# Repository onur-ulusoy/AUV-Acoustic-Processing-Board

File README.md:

# Acoustic Processing Board (APB) Hardware

The Acoustic Processing Board (APB) is a specialized hardware project devoted to processing underwater acoustic signals, captured via hydrophones. This repository houses the electronic design and hardware specifications needed to construct or adapt the APB. Serving as a crucial tool for underwater exploration, navigation, and communication, the APB stands as a testament to innovative engineering solutions. This project is developed for ITU AUV Team.

<picture>    </picture>

<p align="center"><em >APB Filter Test Board</em></p>

<picture>    </picture>

<p align="center">
    
</p>

<p align="center"><em >AUV Electronics 2022</em></p>

<picture>    </picture>

<p align="center">
    
</p>

<picture>    </picture>

<picture>    </picture>

## Table of Contents
- [Acoustic Processing Board (APB) Hardware](#acoustic-processing-board-apb-hardware)
  - [Table of Contents](#table-of-contents)
  - [Project Description](#project-description)
  - [Electronics Design](#electronics-design)
    - [Hydrophone Biasing](#hydrophone-biasing)
    - [Pre-Amplification](#pre-amplification)
    - [6 Pole Butterworth Bandpass Filter](#6-pole-butterworth-bandpass-filter)
    - [Analog Power Supply](#analog-power-supply)
    - [ADC Buffering](#adc-buffering)
  - [Simulation](#simulation)
  - [Filter Test Board](#filter-test-board)
    - [Layer Structure](#layer-structure)
    - [Manufacturing](#manufacturing)
  - [Digital Part](#digital-part)
  - [Technologies Used](#technologies-used)
  - [License](#license)
  - [Project Timeline](#project-timeline)
  - [Gallery](#gallery)

## Project Description

The Acoustic Processing Board (APB) is a pivotal development in the field of Autonomous Underwater Vehicles (AUVs), designed to accurately detect the positions of underwater objects. To optimize performance, APB is split into two distinct parts: an analog PCB and a digital PCB.

The focus of this repository is the analog PCB, which primarily serves as a bandpass filter for frequencies between 25 and 40kHz. This PCB is designed to filter incoming signals from hydrophones before they are passed onto the digital component of the APB. The board was meticulously designed and simulated using LTspice software, featuring components from Analog Devices. The physical layout of the PCB was then accomplished using Altium Designer.

In addition to the analog PCB, there is a complementary digital PCB. This board is responsible for processing the filtered signals from three hydrophones to determine the location of objects underwater. It employs Fast Fourier Transform (FFT) algorithms for signal processing, and is powered by an STM32 microcontroller.

In the interest of thorough testing and performance optimization, the first iteration of the filter PCB was designed for a single hydrophone. This approach enables focused testing on the filtering capabilities, allowing for incremental improvements and fine-tuning of the board's performance before scaling to a three-hydrophone system.

The APB is a testament to innovative design, offering a unique approach to signal processing for AUVs. It represents a significant contribution to our understanding and exploration of underwater environments. We encourage you to explore the repository, understand the design, and contribute to the ongoing development of this cutting-edge technology.

<picture>    </picture>

## Electronics Design

The APB Analog's design is a combination of intricate electronic engineering concepts and high-precision layout work. For an in-depth understanding of its composition, be sure to check the [Full schematics](/LTSpice_Simulation/Full%20Schematic.pdf) and [PCB Schematic Sheets](/Schematic%20Sheets/) These documents not only delineate the arrangement and interconnectivity of the board's components, but also offer insightful details about their specific roles and functionalities. Whether you're interested in the bandpass filtering process, power distribution, or the input/output interfaces, the schematic sheets hold the key to understanding the APB Analog's operational architecture.

### Hydrophone Biasing 

Hydrophone biasing is the first stage in our APB design, and it's vital to the overall functionality of the system. For each of the three hydrophones, a Vhyd- and Vhyd+ and Vcc are the inputs, while Vampin is the output. Importantly, Vhyd- is grounded. This arrangement ensures the correct biasing of the hydrophones, setting the correct operating point for each device and allowing for the effective conversion of underwater acoustic signals into electrical signals.

<p align="center">
    
</p>

### Pre-Amplification

The pre-amplification stage is another essential component of our APB design, ensuring that the electrical signals produced by the hydrophones are amplified adequately for further processing. This stage also employs three separate units, one for each hydrophone. Vampin is used as the input, while Vfin serves as the output. The pre-amplifier is driven by a high precision op-amp, ensuring low-noise amplification and thereby enhancing the clarity and resolution of the captured signals.

<p align="center">
    
</p>

### 6 Pole Butterworth Bandpass Filter

To further process the amplified signals, we employ a 6-pole Butterworth bandpass filter. This filter is replicated three times, once for each hydrophone. The selection of this specific filter topology allows for a flat frequency response in the passband, and a fast roll-off rate, making it highly suitable for our signal processing needs. Appropriate capacitor and resistor values were determined using Analog Devices' application notes. The filter takes Vfin as an input and outputs a filtered signal, Vfout. Each operational amplifier in this stage is referenced with Agnd, which is supplied by the analog power supply circuit.

<p align="center">
    
</p>

### Analog Power Supply

The analog power supply is an integral part of our design. Va is the input, and Agnd is the output. This unit provides the necessary power for all analog sections of the APB. Va and Agnd form the positive and negative poles of the op-amp in the other circuits. By generating a stable and low-noise power supply, this circuit ensures that the operational amplifiers and other analog components function optimally, minimizing signal distortion and maintaining high signal-to-noise ratios.

<p align="center">
    
</p>

### ADC Buffering

ADC buffering serves as the bridge between the analog and digital domains of our APB design. This stage, replicated three times for each hydrophone, takes the filtered signal, Vfout, as input and provides Vadc as output. The buffer, a unity gain amplifier (1x amp), plays a critical role in this system. Its purpose is to isolate the preceding stages from the ADC load. This isolation prevents any impedance mismatch that could degrade the signal quality. By using a buffer, we ensure that the signals processed by the ADC reflect as closely as possible the filtered signals from the bandpass filter stage, enabling accurate digital representation of the original acoustic signals.

<p align="center">
    
</p>

## Simulation

The APB analog subsystem was thoroughly simulated using LTspice, a high-performance SPICE simulator. LTspice offers a variety of capabilities, including enhanced SPICE and an integrated waveform viewer, making it a powerful tool for circuit analysis.

The simulation process involved the use of specific op-amps from Analog Devices. This choice of op-amps was driven by their favorable characteristics, such as low noise, high precision, and their performance within the frequency band of interest.

To ascertain the effectiveness of our 6-pole Butterworth bandpass filter design, we carried out frequency domain analysis. The results are demonstrated in the Bode plot below. As can be seen, the filter provides a passband for frequencies between 25 and 40 kHz, while attenuating frequencies outside this band. This frequency range was chosen specifically to match the operating range of the hydrophones and the acoustic signals they receive.

The simulation results validate the performance of the filter design and provide confidence in its ability to function as intended in the real-world application.

<p align="center">
    
</p>

## Filter Test Board

As part of our development and testing process, we designed a standalone PCB specifically for testing the performance of the filter stage and associated circuits. This board, known as the Filter Test Board, includes only the Butterworth filter, ADC buffering, and pre-amplification circuits, all for just a single hydrophone. 

The Filter Test Board contains crucial components from our original APB analog design that we aimed to test in isolation. We included the Butterworth filter stage, which is the centerpiece of our acoustic processing, to evaluate its frequency response and signal attenuation properties. The Pre-Amplification stage is also included, as it plays a crucial role in enhancing the signals coming from the hydrophone. Additionally, the ADC Buffering stage is incorporated into it. This stage is crucial for isolating the ADC load from the preceding stages, thereby preserving signal integrity. By focusing on these critical parts, the Filter Test Board allows us to verify the operation and performance of the main building blocks of our system without the interference of other elements. As a summary, It is basically includes cruical parts to process one hydrophone signal.

To aid in testing, we've added test points at key output locations like Vampin or Vfin as you can see in the below pcb picture, allowing for easy hook-up of measurement equipment such as oscilloscopes or signal generators. This way, we can inject signals and observe the system's response directly. We gave some voltages such as 1.65V directly to get rid of some power circuits.

Furthermore, we've chosen to use industrial-grade connectors for power supply and signal output. These connectors provide robust, reliable connections, crucial for both testing and eventual deployment.

The schematic diagrams for the Filter Test Board are available in the repository at [PCB Schematic Sheets](/Schematic%20Sheets/). Here, you'll find the full details of the circuits on the test board, providing a wealth of information for understanding and troubleshooting.

Below is top view of the Filter Test Board:

<picture>    </picture>

### Layer Structure

This test version of the APB Analog PCB utilizes a two-layer structure, which has been chosen to simplify the initial stages of testing and troubleshooting. Once the test phase is complete and the design is deemed satisfactory, a transition to a four-layer PCB will take place for the original design. The change in layers not only accommodates the increased complexity of handling signals from three hydrophones simultaneously but also provides better noise isolation and improved signal integrity. Our filter test board's layers can be seen below.

<picture>    </picture>

To understand the depth of the board structure, component placement, and routing of traces, you can check out the [PCB file](/APB_Filter_Test_Board.PrjPcb). It offers a visual representation of the board, aiding in a better understanding of how the circuit's design translates into the physical realm. Keep in mind that this transition from a two-layer board to a four-layer one marks a critical milestone in the evolution of the APB project, embodying the growth from a test concept to a fully-realized, operational piece of hardware.

### Manufacturing

In order to ensure that our Filter Test Board design meets the specific manufacturing specifications of our chosen PCB manufacturer, we have employed the Design Rule Check (DRC) feature in Altium Designer. You can check the detailed report of this rule verification in the output files directory. 

The necessary Gerber files, which include the comprehensive manufacturing details needed to transform our electronic design into a tangible board, are compiled in the [Output](/Output%20Files/) directory.

To date, we have prototyped the Filter Test Board with our manufacturing partner, JLC PCB. Using the invaluable feedback and insights acquired from each iteration, we have continuously refined and improved the design, ensuring it's prepared for rigorous testing and eventual integration into the full Acoustic Processing Board system.

Below you can see some of the pictures of PCBs we manufactured:

<p align="center">
    
</p>

<p align="center">
    
</p>

## Digital Part

The Digital Part represents the second crucial stage of the Acoustic Processing Board (APB). After the Analog Part processes the signals from the hydrophones, it's the responsibility of the Digital Part to receive these analog signals, evaluate them, and ultimately pinpoint the location of the acoustic source underwater.

One of the core operations conducted by the Digital Part involves Fast Fourier Transforms (FFTs). FFTs are a fundamental algorithm in signal processing and analysis, serving to convert a signal from the time domain (where each point represents amplitude at a specific time) into the frequency domain (where each point represents amplitude at a specific frequency). In the context of our APB, we use FFTs to identify the dominant frequencies present in the signals received from the hydrophones, which, when triangulated, can help determine the location of the underwater sound source.

The computational demands of these FFT operations are shouldered by an STM32H743 microcontroller. This powerful microcontroller is well-equipped to handle the processing needs of our board, boasting impressive capabilities, such as handling complex FFT operations and processing data from multiple hydrophones concurrently.

As of the time you're reading this, the development of the Digital Part is still underway. We are committed to achieving a robust, reliable digital signal processing system that effectively complements the analog processing capabilities of the APB. Stay tuned for updates as we continue to progress in this exciting project.

## Technologies Used

- **LTSpice:** At the outset of our design process, we used LTSpice, a high-performance SPICE simulator, for schematic capture and waveform viewer. This tool allowed us to simulate and analyze the behavior of our circuit designs, including the hydrophone biasing, pre-amplification, and filtering stages.

- **Analog Devices Web Applications:** To calculate the optimal values for our 6-Pole Butterworth Bandpass Filter components, we made use of the web applications provided by Analog Devices. These tools were indispensable in ensuring the correct operation of our filters, which play a critical role in the overall performance of the APB.

- **Altium Designer:** Our primary tool for crafting the complex layout of the PCBs was Altium Designer. Its powerful capabilities and intuitive interface allowed us to efficiently design, validate, and prepare the board's electronic components for manufacturing. Its extensive features facilitated the smooth handling of multi-layer board designs.

- **Eagle:** As an alternative to Altium Designer, we also used Autodesk Eagle for some aspects of the design process. Eagle offered us a simpler, more streamlined interface for initial design and testing stages, before transitioning to the more robust Altium Designer for finalizing the intricate multi-layer layout.

- **Fusion 360:** To manage the mechanical design and rendering of the APB, we used Autodesk Fusion 360. This powerful CAD/CAM tool not only allowed us to visualize and perfect the physical design of the board but also helped us ensure its compatibility within the AUV. The integration capabilities of Fusion 360 also facilitated seamless coordination with the mechanical team.

## License

This repository contains the design and documentation for the AUV Acoustic Processing Board, a project by the ITU AUV Team Electonics 2022.

**Licensor:** ITU AUV Team 2022 Electronics

This work is licensed under a [Creative Commons Attribution-NonCommercial-ShareAlike 4.0 International License](http://creativecommons.org/licenses/by-nc-sa/4.0/). You can view the full terms of the license in the [LICENSE](./LICENSE) file in this repository.

**Please note:** When using this project, you must give appropriate credit, including a link to the original GitHub repository: [https://github.com/onur-ulusoy/AUV-Acoustic-Processing-Board](https://github.com/onur-ulusoy/AUV-Acoustic-Processing-Board)

## Project Timeline

This Acoustic Processing Board (APB) project, a significant contribution to the 2022 Electronics Team of ITU AUV (Istanbul Technical University's Autonomous Underwater Vehicle), spanned from December 2021 to August 2022. 

In the initial design and simulation stages of the project, Onur Ulusoy and Sencer Yazıcı diligently worked to create an effective system for processing signals from underwater hydrophones. Their efforts involved comprehensive electronic design and meticulous simulation using LTSpice and Analog Devices' applications. 

Once the design was validated through simulation, the next stage of the project involved the physical realization of the APB. The Filter Test PCB, an essential component of the project, was designed, have manufactured, and typeset by Onur Ulusoy. This crucial testing PCB was brought to life using Altium Designer, with the manufacturing process carried out by JLCPCB. 

While the project was ongoing, thorough documentation was maintained by Onur Ulusoy. His efforts provided an accurate and detailed record of the project, documenting key design decisions, simulation results, and changes made during the PCB design and testing stages. 

As of the current timeline, the Digital Part of the APB, which is designed to receive and analyze the processed signals, is not yet completed. However, the successful development and testing of the APB's analog parts mark significant milestones towards the final goal. 

We are grateful for the invaluable guidance provided by Sencer Yazıcı throughout the development process. His expertise and mentorship played a crucial role in the success of this project. 

Throughout the duration of the Acoustic Processing Board (APB) project, we utilized Trello as our primary project management tool. Trello's intuitive interface and flexible features allowed us to plan, track, and coordinate our tasks effectively. By creating distinct cards for different tasks and using lists to represent different stages of our workflow, we were able to maintain a clear overview of our progress at all times. 

## Gallery

For a visual tour of the APB Filter Test Board PCB, you can explore our [gallery](https://onur-ulusoy.github.io/AUV-Acoustic-Processing-Board/Media/gallery.html). Here you'll find detailed images showcasing the design and implementation of the board.

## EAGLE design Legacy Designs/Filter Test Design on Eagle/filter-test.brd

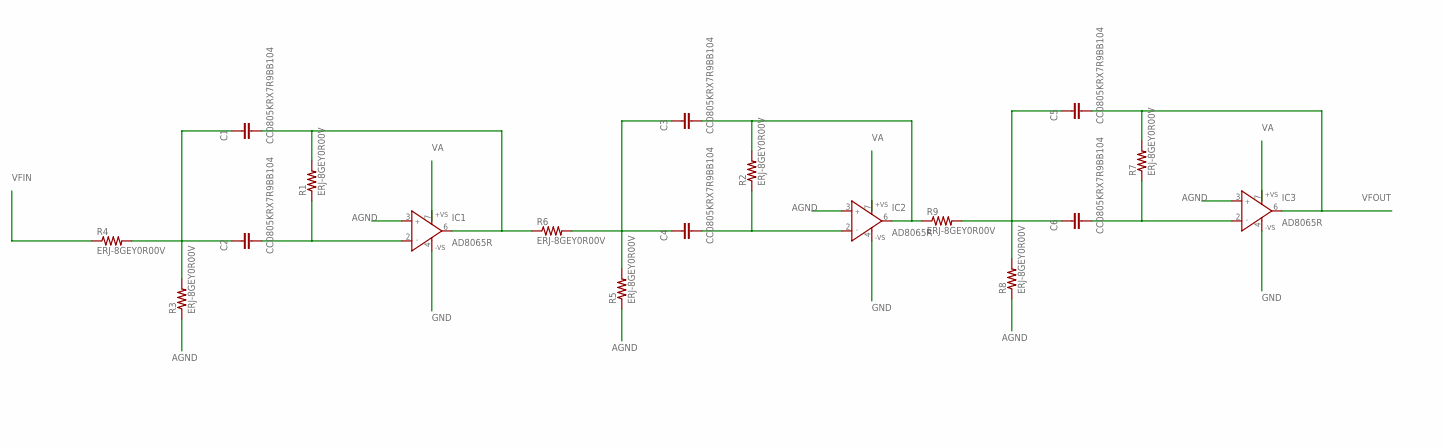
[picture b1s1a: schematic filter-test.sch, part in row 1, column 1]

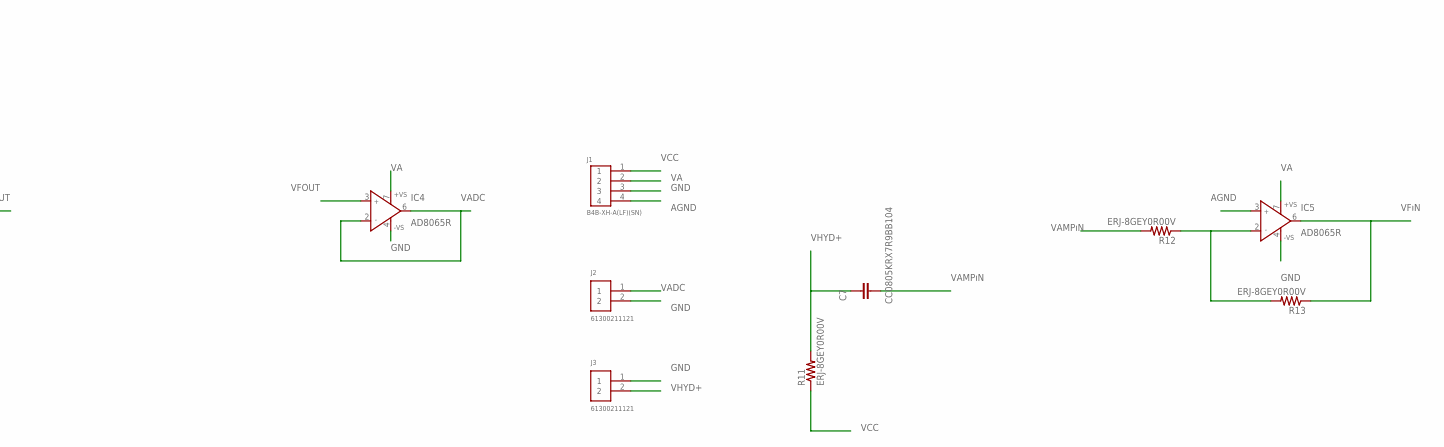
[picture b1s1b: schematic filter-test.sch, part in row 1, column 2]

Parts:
C1, C2, C3, C4, C5, C6, C7: CC0805KRX7R9BB104; CAP_0805
IC1, IC2, IC3, IC4, IC5: AD8065R; SO8
J1: B4B-XH-A(LF)(SN)
J2, J3: 61300211121
R1, R2, R3, R4, R5, R6, R7, R8, R9, R11, R12, R13: ERJ-8GEY0R00V; RES_1206

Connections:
AGND: IC1.3 (IN+), IC2.3 (IN+), IC3.3 (IN+), IC5.3 (IN+), J1.4, R3.1, R5.1, R8.1
GND: IC1.4 (-VS), IC2.4 (-VS), IC3.4 (-VS), IC4.4 (-VS), IC5.4 (-VS), J1.3, J2.2, J3.1
unnamed: C1.1, C2.1, R3.2, R4.2
unnamed: C1.2, IC1.6 (OUT), R1.2, R6.1
unnamed: C2.2, IC1.2 (IN-), R1.1
unnamed: C3.1, C4.1, R5.2, R6.2
unnamed: C3.2, IC2.6 (OUT), R2.2, R9.1
unnamed: C4.2, IC2.2 (IN-), R2.1
unnamed: IC5.2 (IN-), R12.1, R13.2
unnamed: C5.1, C6.1, R8.2, R9.2
unnamed: C6.2, IC3.2 (IN-), R7.1
VA: IC1.7 (+VS), IC2.7 (+VS), IC3.7 (+VS), IC4.7 (+VS), IC5.7 (+VS), J1.2
VADC: IC4.2 (IN-), IC4.6 (OUT), J2.1
VAMPıN: C7.2, R12.2
VCC: J1.1, R11.1
VFIN: R4.1
VFOUT: C5.2, IC3.6 (OUT), IC4.3 (IN+), R7.2
VFıN: IC5.6 (OUT), R13.1
VHYD+: C7.1, J3.2, R11.2

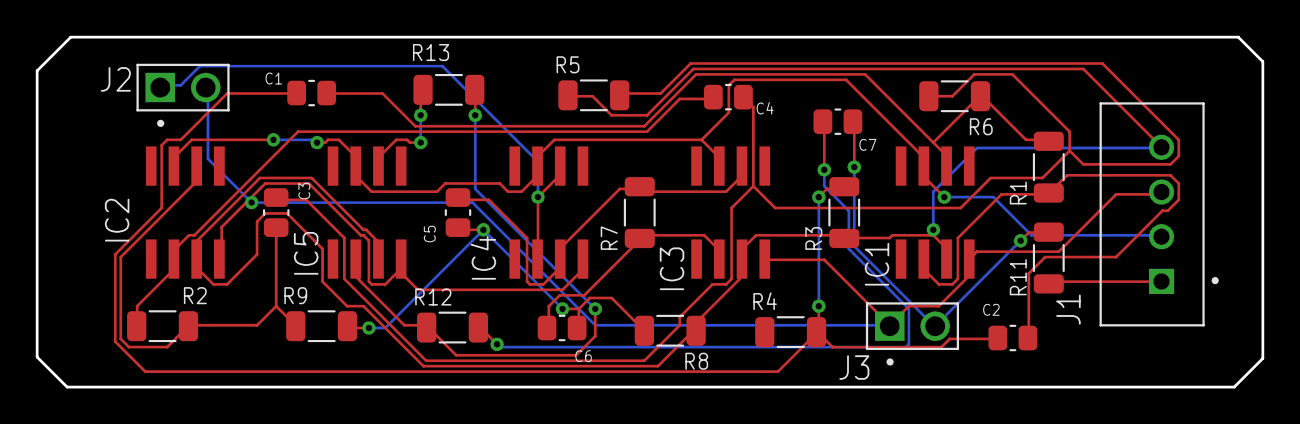
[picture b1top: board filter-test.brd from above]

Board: 2 copper layers, 68.5 x 19.6 mm, 27 parts (0 on the bottom side), 18 nets.

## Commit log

2022-03-23 Init the repository
2022-04-01 Initiate project with APB_Bode artifacts
2022-04-03 Embed APB_Filter schematic representations
2022-04-06 Commit frequency response plots at 15kHz
2022-04-07 Integrate operational amplifier for design visualization
2022-04-08 Incorporate frequency response plots at 35kHz
2022-04-09 Incorporate ceramic capacitor 3D model for design accuracy
2022-04-10 Infuse frequency response plots at 75kHz
2022-04-11 Add PCB connector 3D model for enhanced layout comprehension
2022-04-13 Store APB filter ASC implementation
2022-04-13 Include SMD resistor 3D model for detailed design visualization
2022-04-15 Initialize pcblib with operational amplifier AD8065ARTZ-REEL7
2022-04-16 Log APB filter operations
2022-04-17 Add MLCC CAP 0805_2012 RF to the PCB library
2022-04-18 Commit APB filter raw operational file
2022-04-19 Incorporate MLCC CAP 1206_3216 - 0.8MM into the PCB library
2022-04-20 Consolidate full schematic in PDF format
2022-04-21 Expand PCB library with RES 0805_2012 resistor
2022-04-23 Include RES 1206_3216 RF resistor to the PCB library
2022-04-25 Integrate TO92127P478H483-3 into the PCB library
2022-04-27 Consolidate miscellaneous components into libv1
2022-04-29 Incorporate 2N3819 into schematic library
2022-05-01 Add AD8065ARTZ-REEL7 to schematic library for design consistency
2022-05-05 Initiate schematics with 6 Pole Butterworth Bandpass Filter
2022-05-07 Embed input-output connection schematic for clear representation
2022-05-09 Extend ADC Buffering schematic for precise analog-to-digital conversion
2022-05-11 Establish APB Filter Test Board project for PCB design
2022-05-13 Initiate PCB Document for APB Filter Test Board design
2022-05-15 Provide PCB Design Flow (PCBDwf) for APB Filter Test Board
2022-05-17 Conclude APB Filter Test Board design process with OutJob
2022-05-19 Add .gitignore for clean repository maintenance
2022-05-21 Include APB gold fingers edge connector drawing for reference
2022-05-21 Add general Components and Sales Links v1 document
2022-05-25 Provide Components Sales Links v2 for missing parts
2022-05-27 Integrate EDGE PCB Connector P2.54mm 44pin 2 Rows Right Angle Drawing
2022-05-29 Incorporate PCB Dimensions for clear visualization and manufacturing
2022-05-31 Provide Schematic Sheets-BOM for circuit realization
2022-06-02 Incorporate Design Rule Check reports for APB_Test_Board
2022-06-04 Append Net Status reports for APB_Test_Board
2022-06-06 Append Version1 Gerber Files for PCB manufacturing
2022-06-16 Remove some output files from main branch to prevent confusion
2022-08-18 Include detailed component placements documentation
2022-08-21 Attach comprehensive PCB design information
2022-08-23 Add Legacy APB Design 2021 files for reference
2022-09-01 Add filter-test schematic from Eagle legacy design
2022-09-02 Add filter-test board design from Eagle legacy
2022-09-03 Append 3D model and render from Eagle legacy design
2022-09-07 Initiate README, add necessary pictures to Media
2022-09-07 Write project description, add table of contents
2022-09-07 Write electronics designs sections for part 1
2022-09-09 Complete electronics design part, add all related pictures
2022-09-09 Write simulation and PCB parts
2022-09-09 Complete PCB explanations
2022-09-09 Write manufacturing and digital design parts
2022-09-11 Write project time line and gallery parts, add turnable html for pcb
2022-09-11 Write license and the other parts, complete readme
2022-09-14 Include gallery html code
2022-09-14 Add LICENSE
2022-09-14 Remove html files from master to prevent confusion in github repository
2022-09-14 Update README to fix some render errors
2022-09-14 Update gallery to fix some typos

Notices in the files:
README.md:
License:
This repository contains the design and documentation for the AUV Acoustic Processing Board, a project by the ITU AUV Team Electonics 2022.
Licensor:** ITU AUV Team 2022 Electronics
This work is licensed under a [Creative Commons Attribution-NonCommercial-ShareAlike 4.0 International License](http://creativecommons.org/licenses/by-nc-sa/4.0/). You can view the full terms of the license in the [LICENSE](./LICENSE) file in this repository.
Please note:
